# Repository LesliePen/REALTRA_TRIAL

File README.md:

<h1 align="center">VIKI_PDCU_EGSE_Board</h1>

<p align="center" width="100%">
  
</p>

***

<p align="center">
  
&nbsp; &nbsp; &nbsp; &nbsp;
  
</p>

***

## SPECIFICATIONS

| Parameter | Value | 
| --- | --- |
| Dimensions | 320.0 × 150.0 mm |

***

## DIRECTORY STRUCTURE

    .
    ├─ Computations       # Misc calculations
    ├─ HTML               # HTML files for generated webpage
    ├─ Images             # Pictures and renders
    │
    ├─ kibot_resources    # External resources for KiBot
    │  ├─ colors          # Color theme for KiCad
    │  ├─ fonts           # Fonts used in the project
    │  ├─ scripts         # External scripts used with KiBot
    │  └─ templates       # Templates for KiBot generated reports
    │
    ├─ kibot_yaml         # KiBot YAML config files
    ├─ KiRI               # KiRI (PCB diff viewer) files
    │
    ├─ lib                # KiCad footprint and symbol libraries
    │  ├─ 3d_models       # Component 3D models
    │  ├─ lib_fp          # Footprint libraries
    │  └─ lib_sym         # Symbol libraries
    │
    ├─ Logos              # Logos
    │
    ├─ Manufacturing      # Assembly and fabrication documents
    │  ├─ Assembly        # Assembly documents (BoM, pos, notes)
    │  │
    │  └─ Fabrication     # Fabrication documents (ZIP, notes)
    │     ├─ Drill Tables # CSV drill tables
    │     └─ Gerbers      # Gerbers
    │
    ├─ Report             # Reports for ERC/DRC
    ├─ Schematic          # PDF of schematic
    ├─ Templates          # Title block templates
    ├─ Testing
    │  └─ Testpoints      # Testpoints tables      
    │
    └─ Variants           # Outputs for assembly variants

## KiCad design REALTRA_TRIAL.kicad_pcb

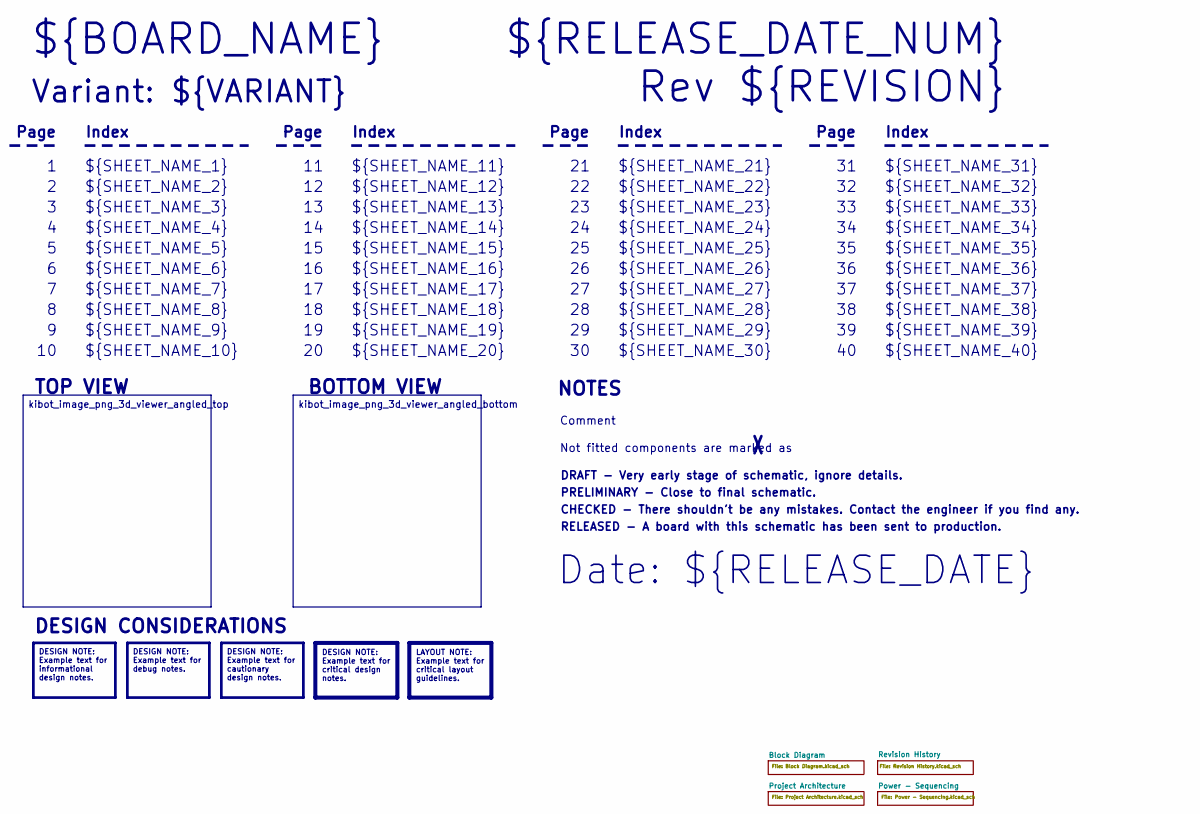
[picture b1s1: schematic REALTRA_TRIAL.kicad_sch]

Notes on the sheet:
Variant: ${VARIANT}
RELEASED - A board with this schematic has been sent to production.
${SHEET_NAME_24}
Index
Page
PRELIMINARY - Close to final schematic.
${SHEET_NAME_22}
DRAFT - Very early stage of schematic, ignore details.
${SHEET_NAME_12}
${SHEET_NAME_8}
${SHEET_NAME_2}
${SHEET_NAME_5}
${SHEET_NAME_20}
${SHEET_NAME_23}
${RELEASE_DATE_NUM}
${SHEET_NAME_35}
Not fitted components are marked as
${SHEET_NAME_11}
${SHEET_NAME_6}
${SHEET_NAME_37}
${SHEET_NAME_26}
${SHEET_NAME_36}
Rev ${REVISION}
${SHEET_NAME_15}
CHECKED - There shouldn't be any mistakes. Contact the engineer if you find any.
BOTTOM VIEW
${SHEET_NAME_14}
${SHEET_NAME_21}
${SHEET_NAME_17}
${SHEET_NAME_18}
Date: ${RELEASE_DATE}
${SHEET_NAME_7}
${SHEET_NAME_31}
${BOARD_NAME}
NOTES
${SHEET_NAME_40}
${SHEET_NAME_39}
${SHEET_NAME_32}
${SHEET_NAME_1}
${SHEET_NAME_9}

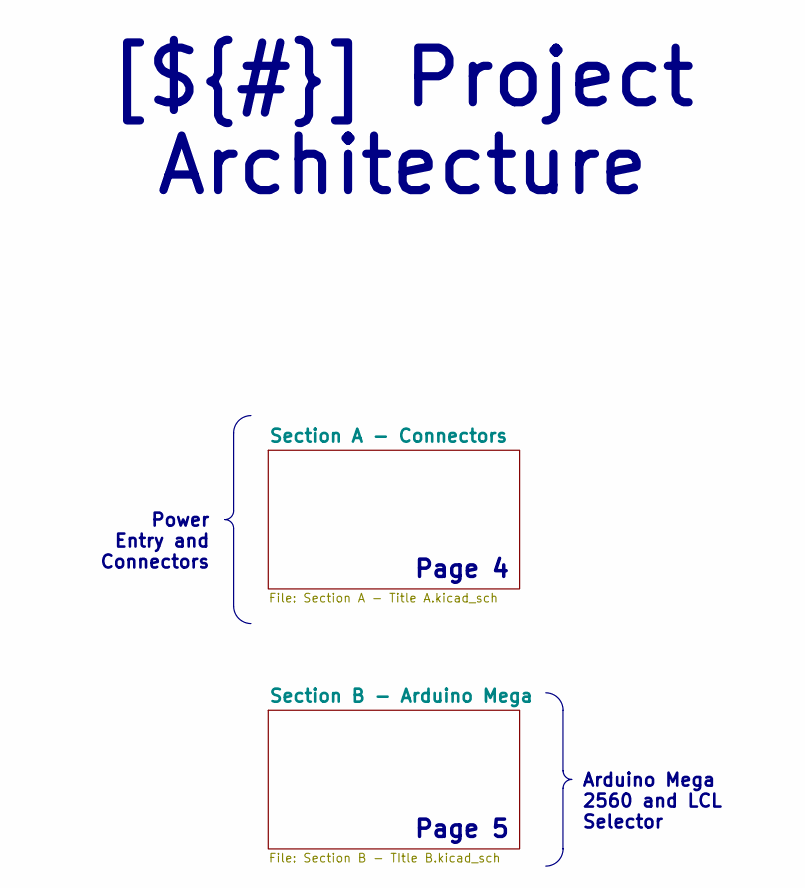
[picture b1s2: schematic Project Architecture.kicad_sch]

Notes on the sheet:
Page 5
Page 4
Power Entry and Connectors
Arduino Mega 2560 and LCL Selector
[${#}] ${TITLE}

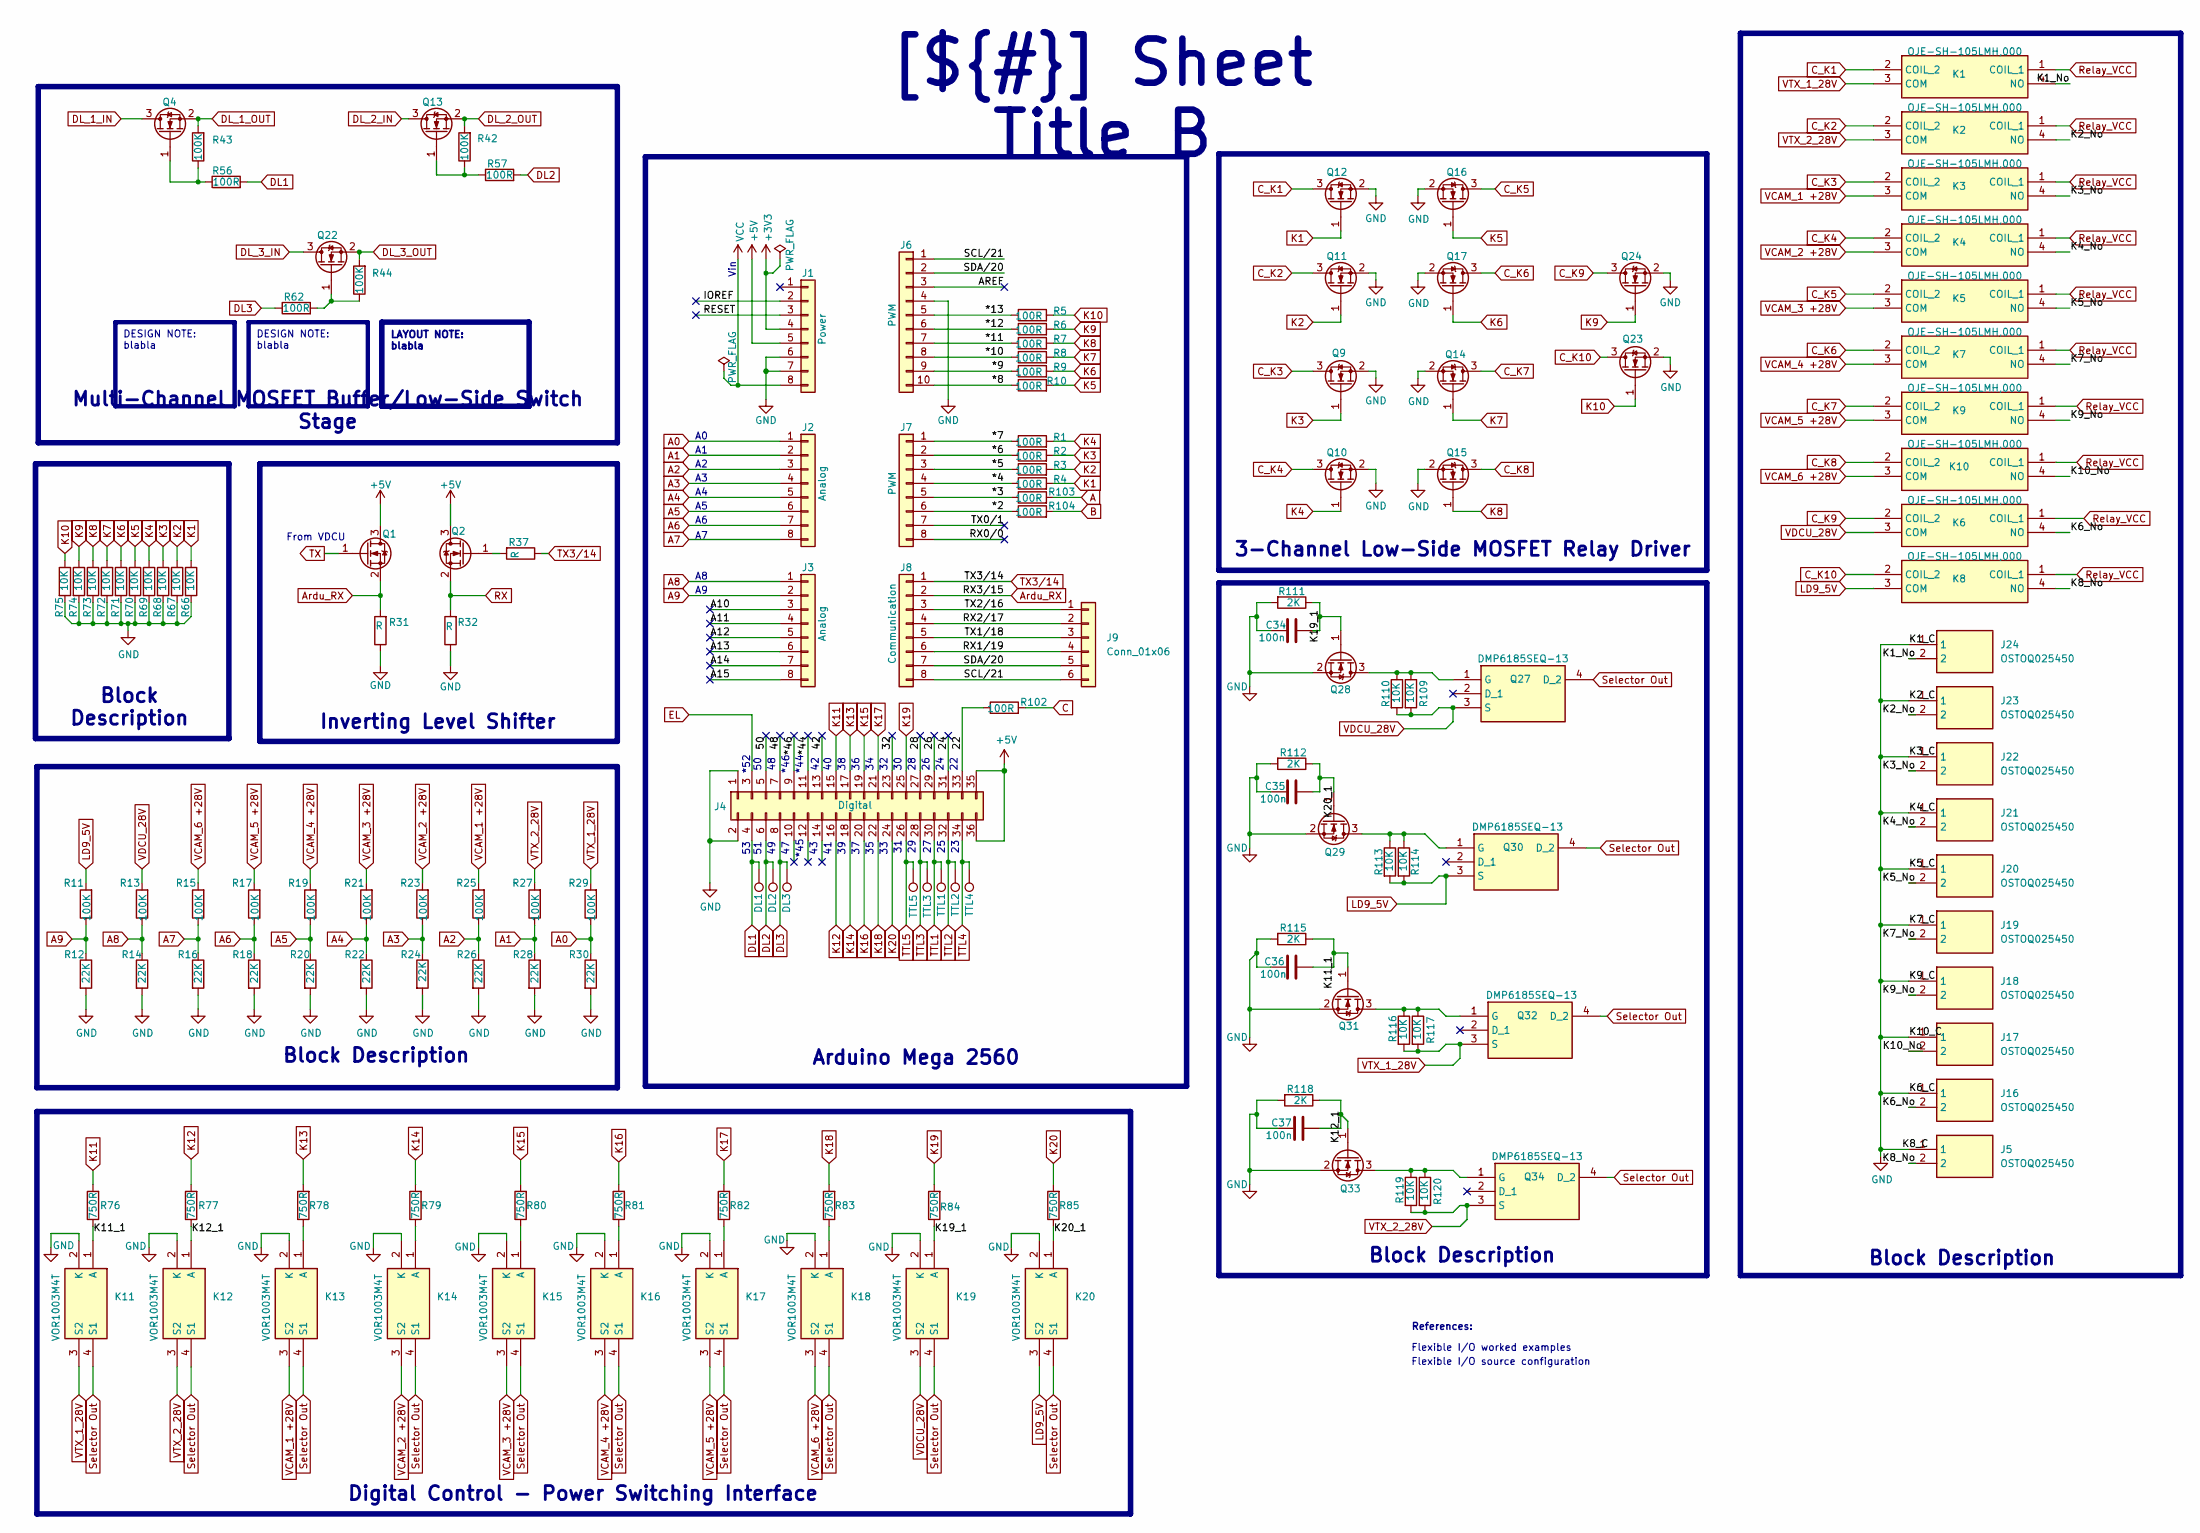
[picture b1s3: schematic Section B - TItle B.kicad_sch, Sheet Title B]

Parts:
C34, C35, C36, C37: 100n; C_0603_1608Metric; Manufacturer Part Number KGM15BR71H104JT
DL1, DL2, DL3: TestPoint; TestPoint_Pad_1.0x1.0mm
J1: Power; PinHeader_1x08_P2.54mm_Vertical
J2, J3: Analog; PinHeader_1x08_P2.54mm_Vertical
J4: Digital; PinHeader_2x18_P2.54mm_Vertical
J5, J16, J17, J18, J19, J20, J21, J22, J23, J24: OSTOQ025450; SHDR2W100P0X508_1X2_1216X860X1230P; Manufacturer_Part_Number OSTOQ025450
J6: PWM; PinHeader_1x10_P2.54mm_Vertical
J7: PWM; PinHeader_1x08_P2.54mm_Vertical
J8: Communication; PinHeader_1x08_P2.54mm_Vertical
J9: Conn_01x06; PinHeader_1x06_P2.54mm_Vertical
K1, K2, K3, K4, K5, K6, K7, K8, K9, K10: OJE-SH-105LMH,000; OJESH105LMH000; Manufacturer_Part_Number OJE-SH-105LMH,000; Mouser Part Number 655-OJE-SH-105LMH000
K11, K12, K13, K14, K15, K16, K17, K18, K19, K20: VOR1003M4T; Manufacturer_Part_Number VOR1003M4T
Q1, Q2, Q4, Q9, Q10, Q11, Q12, Q13, Q14, Q15, Q16, Q17, Q22, Q23, Q24, Q28, Q29, Q31, Q33: IRLML2060; SOT-23; Manufacturer Part Number IRLML2060TRPBF
Q27, Q30, Q32, Q34: DMP6185SEQ-13; SOT230P700X180-4N; Manufacturer_Part_Number DMP6185SEQ-13; Mouser Part Number 621-DMP6185SEQ-13
R1, R2, R3, R4, R5, R6, R7, R8, R9, R10, R56, R57, R62, R102, R103, R104: 100R; R_0805_2012Metric; Manufacturer Part Number CRCW0805100RFKEAHP
R11, R13, R15, R17, R19, R21, R23, R25, R27, R29, R42, R43, R44: 100K; R_0805_2012Metric; Manufacturer Part Number AT0805FRE07100KL
R12, R14, R16, R18, R20, R22, R24, R26, R28, R30: 22K; R_0805_2012Metric; Manufacturer Part Number CRCW080522K0FKEA
R31, R32, R37: R; R_0805_2012Metric
R66, R67, R68, R69, R70, R71, R72, R73, R74, R75, R109, R110, R113, R114, R116, R117, R119, R120: 10K; R_0805_2012Metric; Manufacturer Part Number RC0805FR-0710KL
R76, R77, R78, R79, R80, R81, R82, R83, R84, R85: 750R; R_0805_2012Metric; Manufacturer Part Number RC0805FR-07750RL
R111, R112, R115, R118: 2K; R_0805_2012Metric; Manufacturer Part Number ERJ-P06F2001V
TTL1, TTL2, TTL3, TTL4, TTL5: TestPoint; TestPoint_Pad_1.0x1.0mm

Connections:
+3V3: J1.4
/Project Architecture/Arduino Mega/22: J4.33, R102.1
/Project Architecture/Arduino Mega/24: J4.31
/Project Architecture/Arduino Mega/26: J4.29
/Project Architecture/Arduino Mega/28: J4.27
/Project Architecture/Arduino Mega/32: J4.23
/Project Architecture/Arduino Mega/42: J4.13
/Project Architecture/Arduino Mega/48: J4.7
/Project Architecture/Arduino Mega/50: J4.5
/Project Architecture/Arduino Mega/*2: J7.6, R104.1
/Project Architecture/Arduino Mega/*3: J7.5, R103.1
/Project Architecture/Arduino Mega/*4: J7.4, R4.1
/Project Architecture/Arduino Mega/*5: J7.3, R3.1
/Project Architecture/Arduino Mega/*6: J7.2, R2.1
/Project Architecture/Arduino Mega/*7: J7.1, R1.1
/Project Architecture/Arduino Mega/*8: J6.10, R10.1
/Project Architecture/Arduino Mega/*9: J6.9, R9.1
/Project Architecture/Arduino Mega/*10: J6.8, R8.1
/Project Architecture/Arduino Mega/*11: J6.7, R7.1
/Project Architecture/Arduino Mega/*12: J6.6, R6.1
/Project Architecture/Arduino Mega/*13: J6.5, R5.1
/Project Architecture/Arduino Mega/*44: J4.11
/Project Architecture/Arduino Mega/*46: J4.9
/Project Architecture/Arduino Mega/A10: J3.3
/Project Architecture/Arduino Mega/A11: J3.4
/Project Architecture/Arduino Mega/A12: J3.5
/Project Architecture/Arduino Mega/A13: J3.6
/Project Architecture/Arduino Mega/A14: J3.7
/Project Architecture/Arduino Mega/A15: J3.8
/Project Architecture/Arduino Mega/AREF: J6.3
/Project Architecture/Arduino Mega/IOREF: J1.2
/Project Architecture/Arduino Mega/K1_No: J24.2, K1.4 (NO)
/Project Architecture/Arduino Mega/K2_No: J23.2, K2.4 (NO)
/Project Architecture/Arduino Mega/K3_No: J22.2, K3.4 (NO)
/Project Architecture/Arduino Mega/K4_No: J21.2, K4.4 (NO)
/Project Architecture/Arduino Mega/K5_No: J20.2, K5.4 (NO)
/Project Architecture/Arduino Mega/K6_No: J16.2, K6.4 (NO)
/Project Architecture/Arduino Mega/K7_No: J19.2, K7.4 (NO)
/Project Architecture/Arduino Mega/K8_No: J5.2, K8.4 (NO)
/Project Architecture/Arduino Mega/K9_No: J18.2, K9.4 (NO)
/Project Architecture/Arduino Mega/K10_No: J17.2, K10.4 (NO)
/Project Architecture/Arduino Mega/K11_1: C36.1, K11.1 (A), Q31.1 (G), R76.1, R115.1
/Project Architecture/Arduino Mega/K12_1: C37.1, K12.1 (A), Q33.1 (G), R77.1, R118.1
/Project Architecture/Arduino Mega/K19_1: C34.1, K19.1 (A), Q28.1 (G), R84.1, R111.1
/Project Architecture/Arduino Mega/K20_1: C35.1, K20.1 (A), Q29.1 (G), R85.1, R112.1
/Project Architecture/Arduino Mega/RESET: J1.3
/Project Architecture/Arduino Mega/RX0/0: J7.8
/Project Architecture/Arduino Mega/RX1/19: J8.6, J9.4
/Project Architecture/Arduino Mega/RX2/17: J8.4, J9.2
/Project Architecture/Arduino Mega/SCL/21: J6.1, J8.8, J9.6
/Project Architecture/Arduino Mega/SDA/20: J6.2, J8.7, J9.5
/Project Architecture/Arduino Mega/TX0/1: J7.7
/Project Architecture/Arduino Mega/TX1/18: J8.5, J9.3
/Project Architecture/Arduino Mega/TX2/16: J8.3, J9.1
A: R103.2
A0: J2.1, R29.1, R30.1
A1: J2.2, R27.1, R28.1
A2: J2.3, R25.1, R26.1
A3: J2.4, R23.1, R24.1
A4: J2.5, R21.1, R22.1
A5: J2.6, R19.1, R20.1
A6: J2.7, R17.1, R18.1
A7: J2.8, R15.1, R16.1
A8: J3.1, R13.1, R14.1
A9: J3.2, R11.1, R12.1
Ardu_5V: J1.5, J4.35, J4.36, Q1.3 (D), Q2.3 (D); also elsewhere on the board
Ardu_RX: J8.2, Q1.2 (S), R31.2
B: R104.2
C: R102.2
C_K1: K1.2 (COIL_2), Q12.3 (D)
C_K2: K2.2 (COIL_2), Q11.3 (D)
C_K3: K3.2 (COIL_2), Q9.3 (D)
C_K4: K4.2 (COIL_2), Q10.3 (D)
C_K5: K5.2 (COIL_2), Q16.3 (D)
C_K6: K7.2 (COIL_2), Q17.3 (D)
C_K7: K9.2 (COIL_2), Q14.3 (D)
C_K8: K10.2 (COIL_2), Q15.3 (D)
C_K9: K6.2 (COIL_2), Q24.3 (D)
C_K10: K8.2 (COIL_2), Q23.3 (D)
DL1: DL1.1, J4.4, R56.2
DL2: DL2.1, J4.6, R57.2
DL3: DL3.1, J4.8, R62.1
DL_1_IN: Q4.3 (D); also elsewhere on the board
DL_1_OUT: Q4.2 (S), R43.2; also elsewhere on the board
DL_2_IN: Q13.3 (D); also elsewhere on the board
DL_2_OUT: Q13.2 (S), R42.2; also elsewhere on the board
DL_3_IN: Q22.3 (D); also elsewhere on the board
DL_3_OUT: Q22.2 (S), R44.2; also elsewhere on the board
EL: J4.3; also elsewhere on the board
GND: C34.2, C35.2, C36.2, C37.2, J1.6, J1.7, J4.1, J4.2, J5.1, J6.4, J16.1, J17.1, J18.1, J19.1, J20.1, J21.1, J22.1, J23.1, J24.1, K11.2 (K), K12.2 (K), K13.2 (K), K14.2 (K), K15.2 (K), K16.2 (K), K17.2 (K), K18.2 (K), K19.2 (K), K20.2 (K), Q9.2 (S), Q10.2 (S), Q11.2 (S), Q12.2 (S), Q14.2 (S), Q15.2 (S), Q16.2 (S), Q17.2 (S), Q23.2 (S), Q24.2 (S), Q28.2 (S), Q29.2 (S), Q31.2 (S), Q33.2 (S), R12.2, R14.2, R16.2, R18.2, R20.2, R22.2, R24.2, R26.2, R28.2, R30.2, R31.1, R32.1, R66.2, R67.2, R68.2, R69.2, R70.2, R71.2, R72.2, R73.2, R74.2, R75.2, R111.2, R112.2, R115.2, R118.2; also elsewhere on the board
K1: Q12.1 (G), R4.2, R66.1
K2: Q11.1 (G), R3.2, R67.1
K3: Q9.1 (G), R2.2, R68.1
K4: Q10.1 (G), R1.2, R69.1
K5: Q16.1 (G), R10.2, R70.1
K6: Q17.1 (G), R9.2, R71.1
K7: Q14.1 (G), R8.2, R72.1
K8: Q15.1 (G), R7.2, R73.1
K9: Q24.1 (G), R6.2, R74.1
K10: Q23.1 (G), R5.2, R75.1
K11: J4.15, R76.2
K12: J4.16, R77.2
K13: J4.17, R78.2
K14: J4.18, R79.2
K15: J4.19, R80.2
K16: J4.20, R81.2
K17: J4.21, R82.2
K18: J4.22, R83.2
K19: J4.25, R84.2
K20: J4.24, R85.2
LD9_5V: K8.3 (COM), K20.3 (S2), Q30.3 (S), R11.2, R113.2, R114.2; also elsewhere on the board
unnamed: K13.1 (A), R78.1
unnamed: K14.1 (A), R79.1
unnamed: K15.1 (A), R80.1
unnamed: K16.1 (A), R81.1
unnamed: K17.1 (A), R82.1
unnamed: K18.1 (A), R83.1
unnamed: Q2.1 (G), R37.2
unnamed: Q4.1 (G), R43.1, R56.1
unnamed: Q13.1 (G), R42.1, R57.1
unnamed: Q22.1 (G), R44.1, R62.2
unnamed: Q27.1 (G), Q28.3 (D), R109.1, R110.1
unnamed: Q29.3 (D), Q30.1 (G), R113.1, R114.1
unnamed: Q31.3 (D), Q32.1 (G), R116.1, R117.1
unnamed: Q33.3 (D), Q34.1 (G), R119.1, R120.1
RX: Q2.2 (S), R32.2; also elsewhere on the board
Relay_VCC: K1.1 (COIL_1), K2.1 (COIL_1), K3.1 (COIL_1), K4.1 (COIL_1), K5.1 (COIL_1), K6.1 (COIL_1), K7.1 (COIL_1), K8.1 (COIL_1), K9.1 (COIL_1), K10.1 (COIL_1); also elsewhere on the board
Selector Out: K11.4 (S1), K12.4 (S1), K13.4 (S1), K14.4 (S1), K15.4 (S1), K16.4 (S1), K17.4 (S1), K18.4 (S1), K19.4 (S1), K20.4 (S1), Q27.4 (D_2), Q30.4 (D_2), Q32.4 (D_2), Q34.4 (D_2); also elsewhere on the board
TTL1: J4.30, TTL1.1; also elsewhere on the board
TTL2: J4.32, TTL2.1; also elsewhere on the board
TTL3: J4.28, TTL3.1; also elsewhere on the board
TTL4: J4.34, TTL4.1; also elsewhere on the board
TTL5: J4.26, TTL5.1; also elsewhere on the board
TX: Q1.1 (G); also elsewhere on the board
TX3/14: J8.1, R37.1
VCAM_1 +28V: K3.3 (COM), K13.3 (S2), R25.2; also elsewhere on the board
VCAM_2 +28V: K4.3 (COM), K14.3 (S2), R23.2; also elsewhere on the board
VCAM_3 +28V: K5.3 (COM), K15.3 (S2), R21.2; also elsewhere on the board
VCAM_4 +28V: K7.3 (COM), K16.3 (S2), R19.2; also elsewhere on the board
VCAM_5 +28V: K9.3 (COM), K17.3 (S2), R17.2; also elsewhere on the board
VCAM_6 +28V: K10.3 (COM), K18.3 (S2), R15.2; also elsewhere on the board
VCC: J1.8
VDCU_28V: K6.3 (COM), K19.3 (S2), Q27.3 (S), R13.2, R109.2, R110.2; also elsewhere on the board
VTX_1_28V: K1.3 (COM), K11.3 (S2), Q32.3 (S), R29.2, R116.2, R117.2; also elsewhere on the board
VTX_2_28V: K2.3 (COM), K12.3 (S2), Q34.3 (S), R27.2, R119.2, R120.2; also elsewhere on the board

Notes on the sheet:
*44
Flexible I/O worked examples
*52
From VDCU
References:
*45
Vin
Flexible I/O source configuration
*46
Inverting Level Shifter
Arduino Mega 2560
Block Description
DESIGN NOTE: blabla
[${#}] ${TITLE}
Multi-Channel MOSFET Buffer/Low-Side Switch Stage
3-Channel Low-Side MOSFET Relay Driver
Digital Control - Power Switching Interface
LAYOUT NOTE: blabla

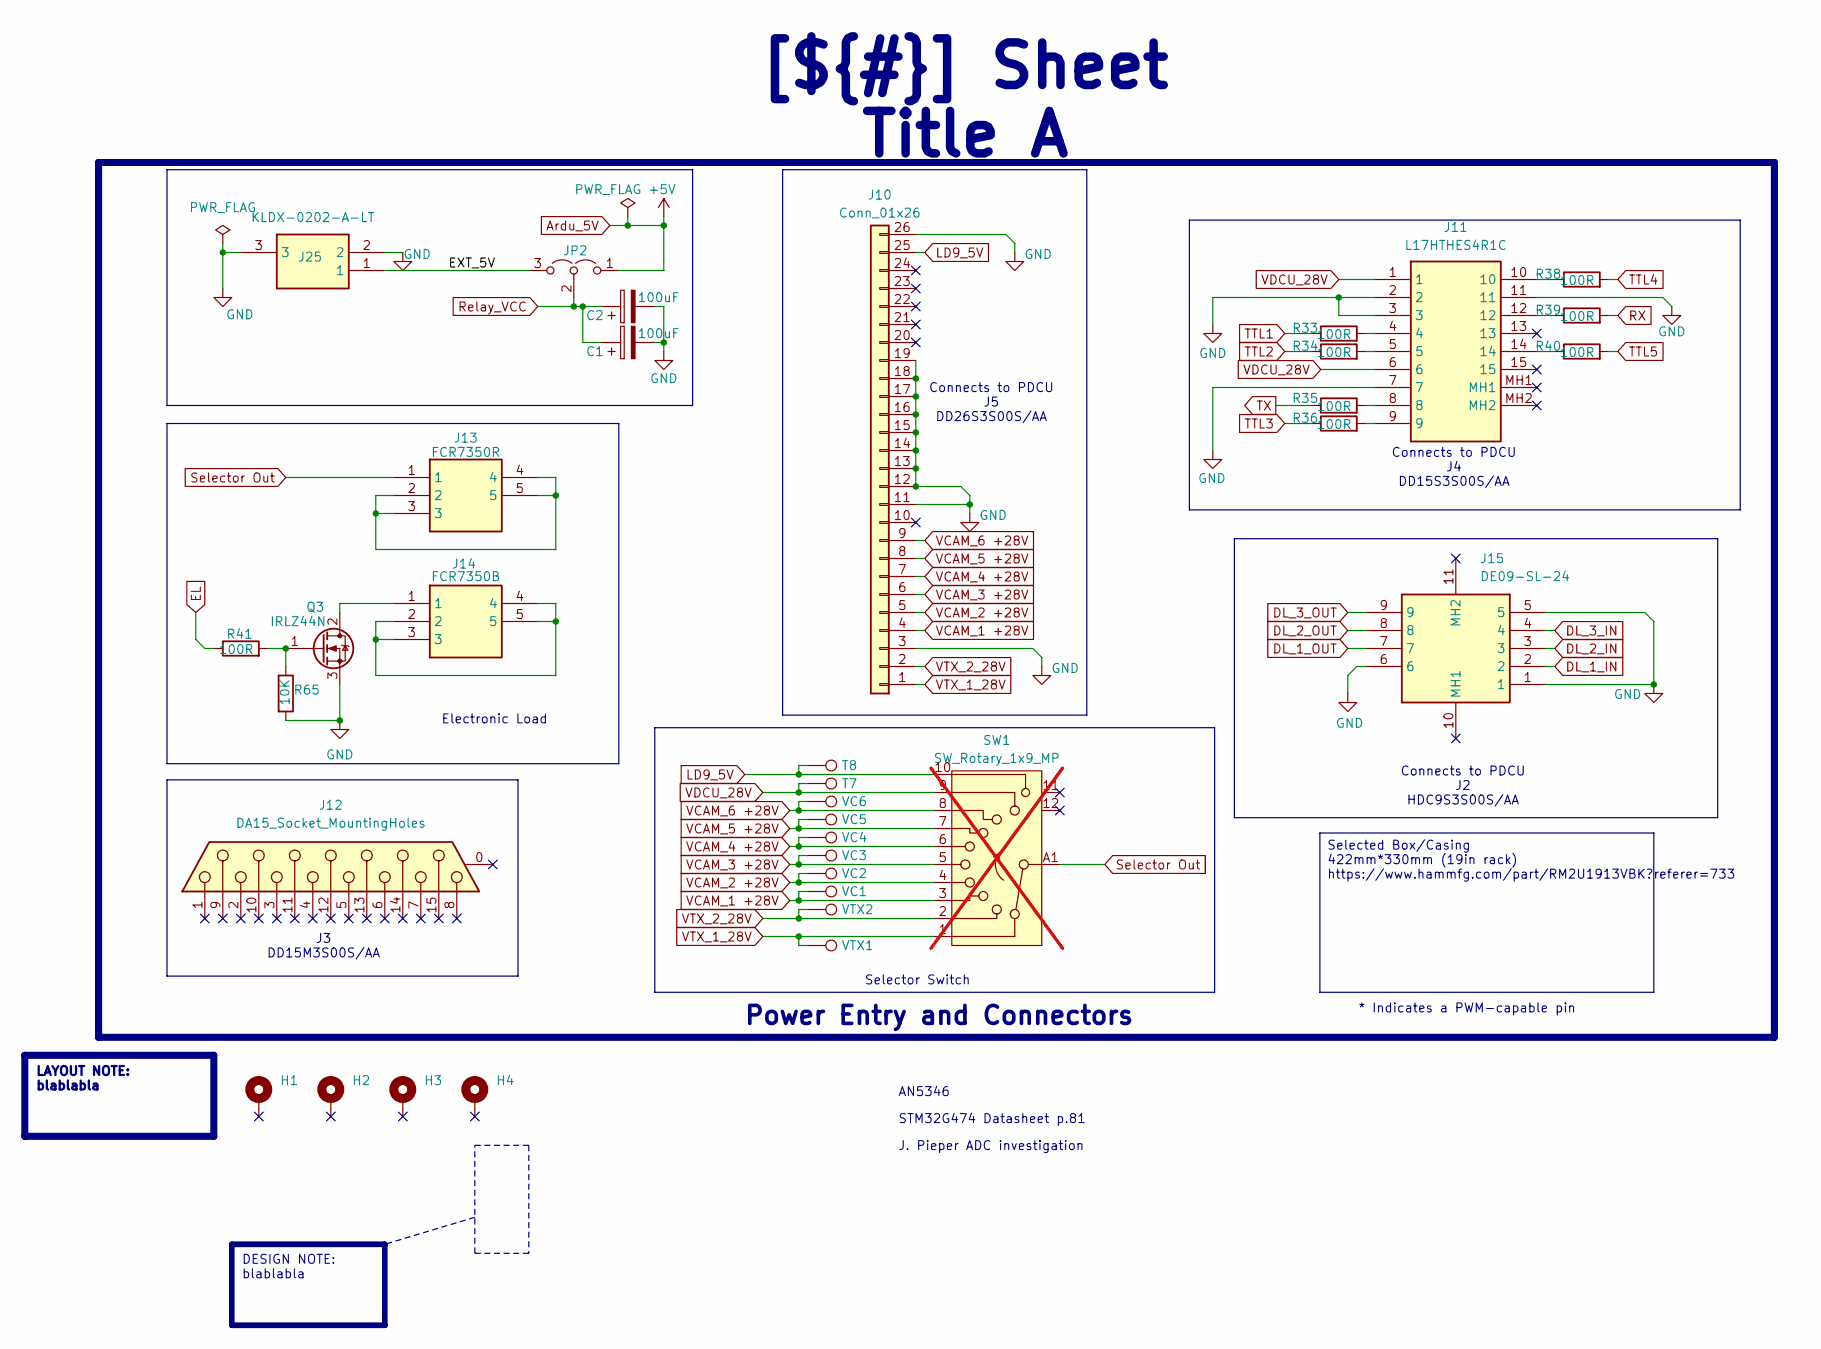
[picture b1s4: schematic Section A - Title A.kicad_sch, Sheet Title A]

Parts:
C1, C2: 100uF; CP_Radial_D7.5mm_P2.50mm; Manufacturer Part Number 875115652007
H1, H2, H3, H4: MountingHole_Pad_MP; MountingHole_3.2mm_M3_DIN965_Pad
J10: Conn_01x26; DSUB-26-HD_Socket_Horizontal_P2.29x2.54mm_EdgePinOffset8.35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; Manufacturer Part Number DD26S3S00S/AA
J11: L17HTHES4R1C; Manufacturer_Part_Number L17HTHES4R1C; Mouser Part Number 523-L17HTHES4R1C
J12: DA15_Socket_MountingHoles; DSUB-15-HD_Pins_Horizontal_P2.29x1.90mm_EdgePinOffset3.03mm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
J13: FCR7350R; Manufacturer_Part_Number FCR7350R
J14: FCR7350B; Manufacturer_Part_Number FCR7350B
J15: DE09-SL-24; DE09SL24; Manufacturer_Part_Number DE09-SL-24
J25: KLDX-0202-A-LT; KLDX0202ALT; Manufacturer_Part_Number KLDX-0202-A-LT; Mouser Part Number 806-KLDX-0202-A-LT
JP2: Jumper_3_Open; PinHeader_1x03_P2.54mm_Vertical
Q3: IRLZ44N; TO-220-3_Horizontal_TabDown; Manufacturer Part Number IRLZ44NPBF
R33, R34, R35, R36, R38, R39, R40, R41: 100R; R_0805_2012Metric; Manufacturer Part Number CRCW0805100RFKEAHP
R65: 10K; R_0805_2012Metric; Manufacturer Part Number RC0805FR-0710KL
SW1: SW_Rotary_1x9_MP; CK1059; Manufacturer Part Number CK1059; not fitted
T7, T8: TestPoint; TestPoint_Pad_0.6x0.6mm
VC1, VC2, VC3, VC4, VC5, VC6: TestPoint; TestPoint_Pad_0.6x0.6mm
VTX1, VTX2: TestPoint; TestPoint_Pad_1.0x1.0mm

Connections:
/Project Architecture/Connectors/EXT_5V: J25.1, JP2.3 (B)
Ardu_5V: JP2.1 (A); also elsewhere on the board
DL_1_IN: J15.2; also elsewhere on the board
DL_1_OUT: J15.7; also elsewhere on the board
DL_2_IN: J15.3; also elsewhere on the board
DL_2_OUT: J15.8; also elsewhere on the board
DL_3_IN: J15.4; also elsewhere on the board
DL_3_OUT: J15.9; also elsewhere on the board
EL: R41.1; also elsewhere on the board
GND: C1.2, C2.2, J10.3, J10.11, J10.12, J10.13, J10.14, J10.15, J10.16, J10.17, J10.18, J10.19, J10.26, J11.2, J11.3, J11.7, J11.11, J15.1, J15.5, J15.6, J25.2, J25.3, Q3.3 (S), R65.2; also elsewhere on the board
LD9_5V: J10.25, SW1.10, T8.1; also elsewhere on the board
unnamed: J11.4, R33.2
unnamed: J11.5, R34.2
unnamed: J11.8, R35.2
unnamed: J11.9, R36.2
unnamed: J11.10, R38.1
unnamed: J11.12, R39.1
unnamed: J11.14, R40.1
unnamed: J13.2, J13.3, J13.4, J13.5
unnamed: J14.2, J14.3, J14.4, J14.5
unnamed: J14.1, Q3.2 (D)
unnamed: Q3.1 (G), R41.2, R65.1
RX: R39.2; also elsewhere on the board
Relay_VCC: C1.1, C2.1, JP2.2 (C); also elsewhere on the board
Selector Out: J13.1, SW1.A1; also elsewhere on the board
TTL1: R33.1; also elsewhere on the board
TTL2: R34.1; also elsewhere on the board
TTL3: R36.1; also elsewhere on the board
TTL4: R38.2; also elsewhere on the board
TTL5: R40.2; also elsewhere on the board
TX: R35.1; also elsewhere on the board
VCAM_1 +28V: J10.4, SW1.3, VC1.1; also elsewhere on the board
VCAM_2 +28V: J10.5, SW1.4, VC2.1; also elsewhere on the board
VCAM_3 +28V: J10.6, SW1.5, VC3.1; also elsewhere on the board
VCAM_4 +28V: J10.7, SW1.6, VC4.1; also elsewhere on the board
VCAM_5 +28V: J10.8, SW1.7, VC5.1; also elsewhere on the board
VCAM_6 +28V: J10.9, SW1.8, VC6.1; also elsewhere on the board
VDCU_28V: J11.1, J11.6, SW1.9, T7.1; also elsewhere on the board
VTX_1_28V: J10.1, SW1.1, VTX1.1; also elsewhere on the board
VTX_2_28V: J10.2, SW1.2, VTX2.1; also elsewhere on the board

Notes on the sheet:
J3 DD15M3S00S/AA
Connects to PDCU J4 DD15S3S00S/AA
Connects to PDCU J2 HDC9S3S00S/AA
Selector Switch
Electronic Load
J. Pieper ADC investigation
Connects to PDCU J5 DD26S3S00S/AA
STM32G474 Datasheet p.81
AN5346
* Indicates a PWM-capable pin
Power Entry and Connectors
Selected Box/Casing 422mm*330mm (19in rack) https://www.hammfg.com/part/RM2U1913VBK?referer=733
DESIGN NOTE: blablabla
[${#}] ${TITLE}
LAYOUT NOTE: blablabla

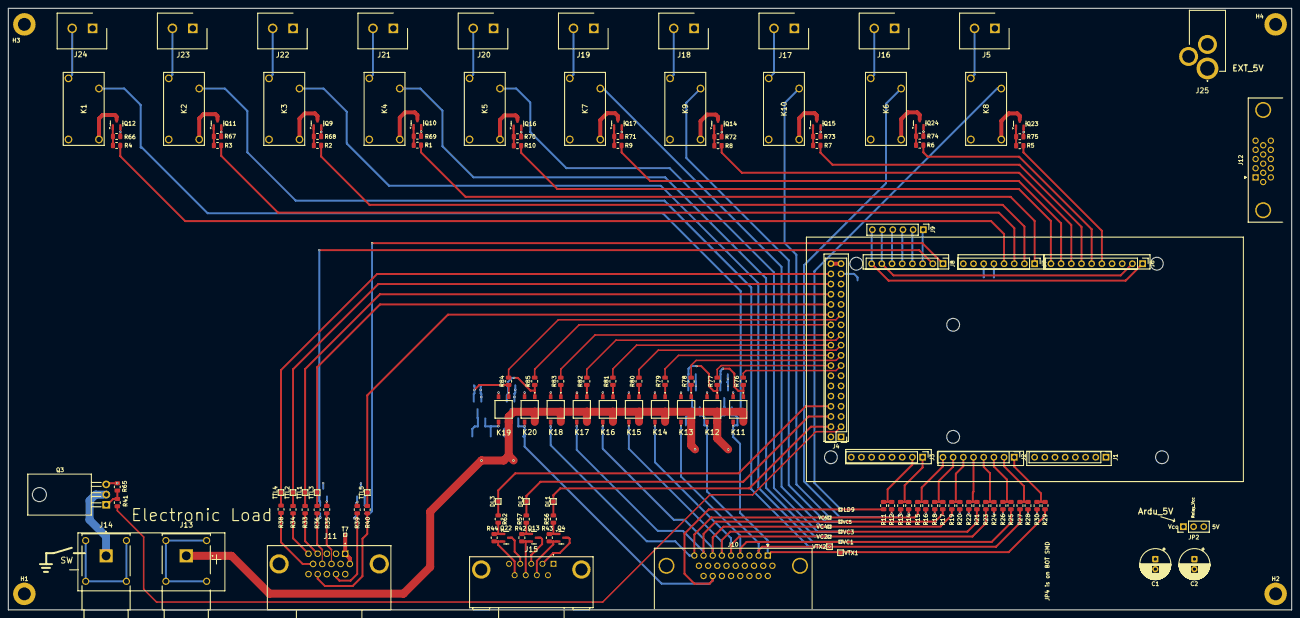
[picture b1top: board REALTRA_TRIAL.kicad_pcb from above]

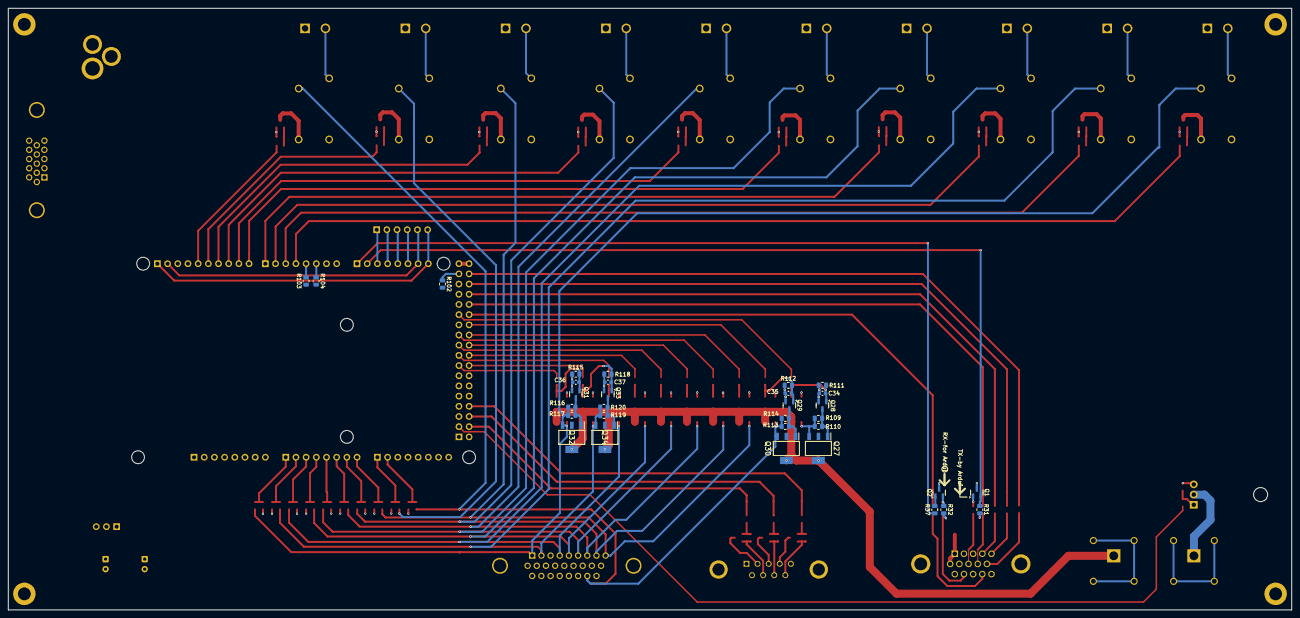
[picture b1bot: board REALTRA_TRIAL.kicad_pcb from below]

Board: 4 copper layers, 320.0 x 150.0 mm, 187 parts (38 on the bottom side), 132 nets.

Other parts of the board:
MH1, MH2, MH3, MH4, MH5, MH6: MountingHole_3.2mm

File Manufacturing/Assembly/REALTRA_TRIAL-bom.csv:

Row,REALTRA Part Number,Quantity Per PCB,References,Value,Datasheet,Footprint,Description,Manufacturer,Manufacturer Part Number,Supplier Part Number
1,R-CAP-0051-100N,4,C34 C35 C36 C37,100n,~,C_0603_1608Metric,Unpolarized capacitor,KYOCERA AVX,KGM15BR71H104JT,
2,R-CON-1265-9POS,1,J15,DE09-SL-24,https://app.adam-tech.com/products/download/data_sheet/19847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,DE09SL24,"9 Position D-Sub Receptacle, Female Sockets Connector 250VAC ,3A,-20C ~ 85C",,,
3,R-CON-1267-BBLK,1,J14,FCR7350B,https://www.cliffuk.co.uk/products/testleads/sockets/S16NPC.pdf,FCR7350B,"Banana Jack Connector Standard Banana Solder Black Female  Through Hole, Right Angle",,,
4,R-CON-1266-BRED,1,J13,FCR7350R,http://www.cliffuk.co.uk/products/testleads/sockets/S16NPC.pdf,FCR7350R,"CLIFF ELECTRONIC COMPONENTS - FCR7350R - SOCKET, PCB, 4MM, R/A, S16N-PC, RED",,,
5,R-CON-1264-15PO,1,J11,L17HTHES4R1C,https://cdn.amphenol-cs.com/media/wysiwyg/files/drawing/l17h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,L17HTHES4R1C,"Dsub, Stamped Signal 3A, Right Angle PCB Thru Hole, Hight Temp High Density, FP=8.89mm (0.350in), 15 Socket, Bright Tin Shell, Flash Gold, 4-40 Rear Insert, Ground Tab&Boardlock, Plastic Tray, Close Back",,,
6,R-CON-1262-VTBH,10,J5 J16 J17 J18 J19 J20 J21 J22 J23 J24,OSTOQ025450,https://www.on-shore.com/wp-content/uploads/OSTOQXX5450.pdf,SHDR2W100P0X508_1X2_1216X860X1230P,TERM BLOCK HDR 2POS VERT 5.08MM,,,
7,R-CON-1263-26PO,10,J1 J2 J3 J4 J6 J7 J8 J9 J10 J12,Power,~,PinHeader_1x08_P2.54mm_Vertical,"Generic connector, single row, 01x08, script generated (kicad-library-utils/schlib/autogen/connector/) Generic connector, double row, 02x18, odd/even pin numbering scheme (row 1 odd numbers, row 2 even numbers), script generated (kicad-library-utils/schlib/autogen/connector/) Generic connector, single row, 01x10, script generated (kicad-library-utils/schlib/autogen/connector/) Generic connector, single row, 01x06, script generated (kicad-library-utils/schlib/autogen/connector/) Generic connector, single row, 01x26, script generated (kicad-library-utils/schlib/autogen/connector/) 15-pin D-SUB connector, socket (female) (low-density/2 columns), Mounting Hole",Amphenol Positronic,DD26S3S00S/AA,
8,R-SWI-0002-RESW,10,K1 K2 K3 K4 K5 K6 K7 K8 K9 K10,"OJE-SH-105LMH,000",https://www.te.com/commerce/DocumentDelivery/DDEController?A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,OJESH105LMH000,Body Features: Product Weight .318 OZ | Product Weight 9 G | Insulation Special Features Tracking Index of Relay Base PTI250 | Contact Features: Contact Material AgCdO | Contact Current Class 16 AMP | Contact Arrangement 1 Form A (NO) | Contact Number of Poles 1 | Contact Current Rating (Max) 8 AMP | Dimensions: Insulation Clearance Between Contact & Coil .129 INCH | Length Class (Mechanical) 16  20 MM | Height Class (Mechanical) 14  15 MM | Product Height 14.7 MM | Product Length .716 INCH | Product,,,
9,R-SWI-0003-PRSW,10,K11 K12 K13 K14 K15 K16 K17 K18 K19 K20,VOR1003M4T,https://www.digikey.com/en/products/detail/vishay-semiconduc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,VOR1003M4T,"Solid State SPST-NO (1 Form A) 4-SMD, Gull Wing",,,
10,R-FET-0023-PCMF,4,Q27 Q30 Q32 Q34,DMP6185SEQ-13,https://www.diodes.com//assets/Datasheets/DMP6185SEQ.pdf,SOT230P700X180-4N,MOSFET MOSFET BVDSS: 41V-60V,,,
11,R-FET-0021-NCMF,19,Q1 Q2 Q4 Q9 Q10 Q11 Q12 Q13 Q14 Q15 Q16 Q17 Q22 Q23 Q24 Q28 Q29 Q31 Q33,IRLML2060,https://www.infineon.com/dgdl/irlml2060pbf.pdf?fileId=5546d4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,SOT-23,"1.2A Id, 60V Vds, 480mOhm Rds, N-Channel HEXFET Power MOSFET, SOT-23",Infineon Technologies,IRLML2060TRPBF,
12,R-FET-0022-NCTO,1,Q3,IRLZ44N,http://www.irf.com/product-info/datasheets/data/irlz44n.pdf,TO-220-3_Horizontal_TabDown,"47A Id, 55V Vds, 22mOhm Rds Single N-Channel HEXFET Power MOSFET, TO-220AB",Infineon Technologies,IRLZ44NPBF,
13,,3,R31 R32 R37,R,~,R_0805_2012Metric,Resistor,,,
14,R-RES-0388-100R,24,R1 R2 R3 R4 R5 R6 R7 R8 R9 R10 R33 R34 R35 R36 R38 R39 R40 R41 R56 R57 R62 R102 R103 R104,100R,~,R_0805_2012Metric,Resistor,VISHAY,CRCW0805100RFKEAHP,
15,R-RES-0518-750R,10,R76 R77 R78 R79 R80 R81 R82 R83 R84 R85,750R,~,R_0805_2012Metric,Resistor,YAGEO,RC0805FR-07750RL,
16,R-RES-0519-2KR,4,R111 R112 R115 R118,2K,~,R_0805_2012Metric,Resistor,Panasonic Electronic Components,ERJ-P06F2001V,
17,R-RES-0122-10K,19,R65 R66 R67 R68 R69 R70 R71 R72 R73 R74 R75 R109 R110 R113 R114 R116 R117 R119 R120,10K,~,R_0805_2012Metric,Resistor,Yageo,RC0805FR-0710KL,
18,R-RES-0520-22KR,10,R12 R14 R16 R18 R20 R22 R24 R26 R28 R30,22K,~,R_0805_2012Metric,Resistor,Vishay Dale,CRCW080522K0FKEA,
19,R-RES-0124-100K,13,R11 R13 R15 R17 R19 R21 R23 R25 R27 R29 R42 R43 R44,100K,~,R_0805_2012Metric,Resistor,YAGEO,AT0805FRE07100KL,

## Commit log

2026-02-09 First draft of the schematic
2026-02-09 Update Outputs
2026-02-09 First draft of PCB Preliminary version
